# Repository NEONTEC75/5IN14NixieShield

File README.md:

# 5IN14NixieShield
This shield is just a minimal Nixie multiplexed circuit and contains the following components:
- 74141 nixie cathode driver IC (pins 4, 6, 7, 5);
- TLP627 opto-couplers for anodes (pins 12, 11, 9, 8, 10);
- 3-button resistive keyboard (A3);
- simple boost converter driven by Arduino's PWM (pin 3, and pin A0 for output voltage feedback);
- DS3231 module connector.

The library with some examples:
https://github.com/NEONTEC75/Nixie

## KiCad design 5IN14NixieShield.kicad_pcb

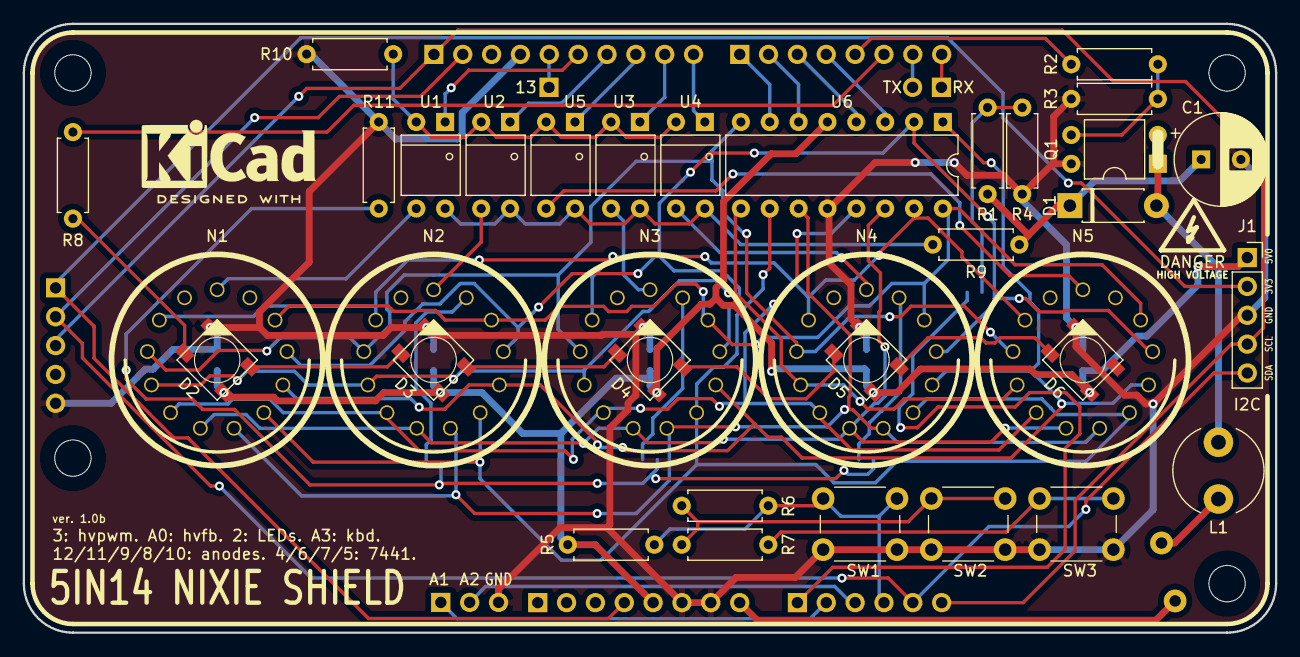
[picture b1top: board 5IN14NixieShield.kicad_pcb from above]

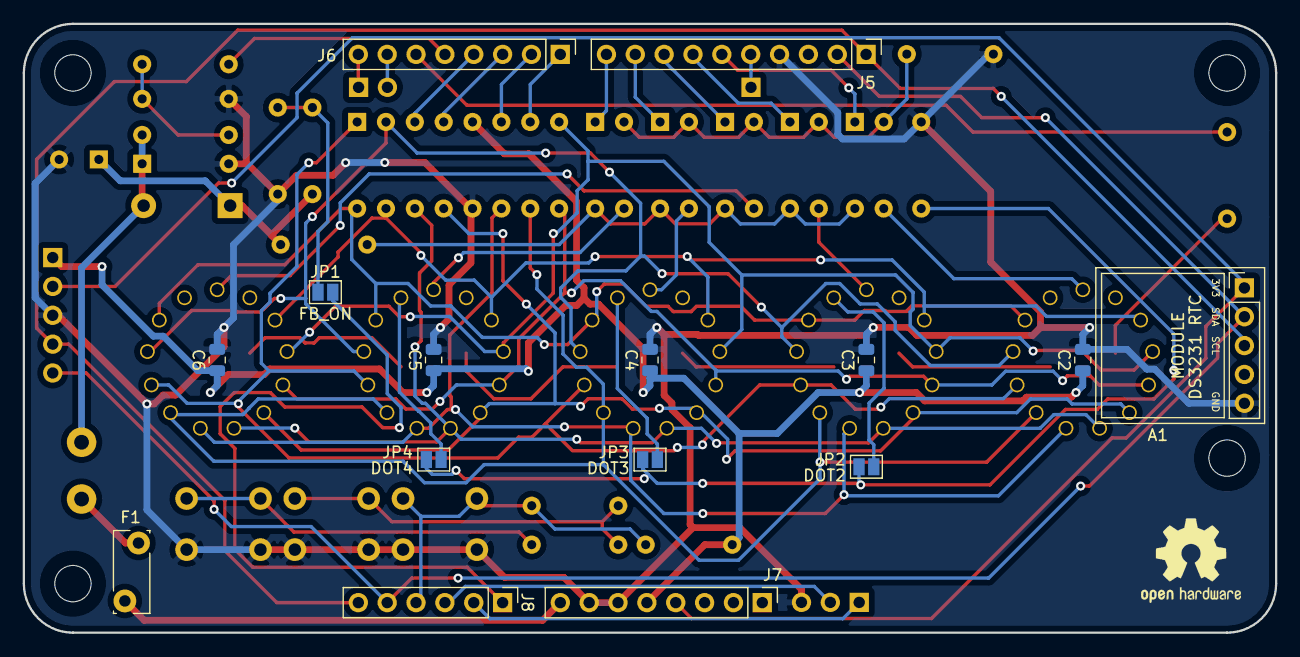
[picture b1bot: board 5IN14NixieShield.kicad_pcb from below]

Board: 2 copper layers, 110.2 x 53.6 mm, 59 parts (16 on the bottom side), 57 nets.

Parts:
A1: DS3231
C1: 4.7uF*350V; CP_Radial_D8.0mm_P3.50mm
C2, C3, C4, C5, C6: 100n; C_0805_2012Metric
D1: HER106; D_DO-41_SOD81_P7.62mm_Horizontal
D2, D3, D4, D5, D6: WS2812B
F1: 1A; Fuse_Bourns_MF-RG300
H1, H2, H3, H4: MountingHole; MountingHole_3.2mm_M3_DIN965
J1: I2C; PinSocket_1x05_P2.54mm_Vertical
J3: 13; PinHeader_1x01_P2.54mm_Vertical
J4: EXT2; PinHeader_1x02_P2.54mm_Vertical
J5: UNO3; PinHeader_1x10_P2.54mm_Vertical
J6: UNO4; PinHeader_1x08_P2.54mm_Vertical
J7: UNO1; PinHeader_1x08_P2.54mm_Vertical
J8: UNO2; PinHeader_1x06_P2.54mm_Vertical
J9: EXT1; PinHeader_1x03_P2.54mm_Vertical
JP1: FB_ON; SolderJumper-2_P1.3mm_Open_Pad1.0x1.5mm
JP2: DOT2; SolderJumper-2_P1.3mm_Open_Pad1.0x1.5mm
JP3: DOT3; SolderJumper-2_P1.3mm_Open_Pad1.0x1.5mm
JP4: DOT4; SolderJumper-2_P1.3mm_Open_Pad1.0x1.5mm
KICADLOGO: KiCad-Logo2_6mm_SilkScreen
L1: 470uH; L_Radial_D7.8mm_P5.00mm_Fastron_07HCP
N1, N2, N3, N4, N5: IN-14; IN-14new
OSHW1: OSHW-Logo2_9.8x8mm_SilkScreen
Q1: IRFD220; DIP-4_FET
R1: 300k; R_Axial_DIN0207_L6.3mm_D2.5mm_P7.62mm_Horizontal
R2: 22; R_Axial_DIN0207_L6.3mm_D2.5mm_P7.62mm_Horizontal
R3: 100k; R_Axial_DIN0207_L6.3mm_D2.5mm_P7.62mm_Horizontal
R4: 4k7; R_Axial_DIN0207_L6.3mm_D2.5mm_P7.62mm_Horizontal
R5, R6, R7: 10k; R_Axial_DIN0207_L6.3mm_D2.5mm_P7.62mm_Horizontal
R8: 100; R_Axial_DIN0207_L6.3mm_D2.5mm_P7.62mm_Horizontal
R9: 2k2; R_Axial_DIN0207_L6.3mm_D2.5mm_P7.62mm_Horizontal
R10: 470; R_Axial_DIN0207_L6.3mm_D2.5mm_P7.62mm_Horizontal
R11: 10k*; R_Axial_DIN0207_L6.3mm_D2.5mm_P7.62mm_Horizontal
SW1, SW2, SW3: SW_Push; SW_PUSH_6mm_H4.3mm
U1, U2, U3, U4, U5: TLP627
U6: K155ID1; DIP-16_W7.62mm

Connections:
+3V3: A1.1, J1.2, J7.4
+5V: C2.1, C3.1, C4.1, C5.1, C6.1, D2.1, D3.1, D4.1, D5.1, D6.1, J1.1, J7.5, R5.1, U6.5
/+HV: C1.1, D1.1, R1.2, R9.1
/A0: J8.1, JP1.2
/A1: J8.2, J9.1
/A2: J8.3, J9.2
/A3: J8.4, R5.2, R6.1, SW1.1
/A4: A1.2, J1.5, J5.2, J8.5
/A5: A1.3, J1.4, J5.1, J8.6
/ACTL_1: J5.6, U1.1
/ACTL_2: J5.7, U2.1
/ACTL_3: J5.9, U3.1
/ACTL_4: J5.10, U4.1
/ACTL_DOT: J5.8, U5.1
/BOOST_PWM: J6.5, R2.2
/D0: J4.1, J6.8
/D1: J4.2, J6.7
/D2: J6.6, R8.1
/D4: J6.4, U6.3
/D5: J6.3, U6.4
/D6: J6.2, U6.6
/D7: J6.1, U6.7
/D13: J3.1, J5.5
/NixieCtl/ANODE_1: N1.A, U1.3
/NixieCtl/ANODE_2: N2.A, U2.3
/NixieCtl/ANODE_3: N3.A, U3.3
/NixieCtl/ANODE_4: N4.A, U4.3
/NixieCtl/ANODE_5: N5.A, U5.3
/NixieCtl/CATHODE_0: N1.0, N2.0, N3.0, N4.0, N5.0, U6.16
/NixieCtl/CATHODE_1: N1.1, N2.1, N3.1, N4.1, N5.1, U6.15
/NixieCtl/CATHODE_2: N1.2, N2.2, N3.2, N4.2, N5.2, U6.8
/NixieCtl/CATHODE_3: N1.3, N2.3, N3.3, N4.3, N5.3, U6.9
/NixieCtl/CATHODE_4: N1.4, N2.4, N3.4, N4.4, N5.4, U6.13
/NixieCtl/CATHODE_5: N1.5, N2.5, N3.5, N4.5, N5.5, U6.14
/NixieCtl/CATHODE_6: N1.6, N2.6, N3.6, N4.6, N5.6, U6.11
/NixieCtl/CATHODE_7: N1.7, N2.7, N3.7, N4.7, N5.7, U6.10
/NixieCtl/CATHODE_8: N1.8, N2.8, N3.8, N4.8, N5.8, U6.1
/NixieCtl/CATHODE_9: N1.9, N2.9, N3.9, N4.9, N5.9, U6.2
/VIN: F1.1, J7.8
GND: A1.5, C1.2, C2.2, C3.2, C4.2, C5.2, C6.2, D2.3, D3.3, D4.3, D5.3, D6.3, J1.3, J5.4, J7.6, J7.7, J9.3, Q1.3, R3.2, R4.1, R10.2, R11.1, SW1.2, SW2.2, SW3.2, U6.12
unnamed: D1.2, L1.1, Q1.2
unnamed: D2.2, D3.4
unnamed: D2.4, R8.2
unnamed: D3.2, D4.4
unnamed: D4.2, D5.4
unnamed: D5.2, D6.4
unnamed: F1.2, L1.2
unnamed: JP1.1, R1.1, R4.2
unnamed: JP2.1, N2.RHDP
unnamed: JP2.2, JP3.2, JP4.2, R11.2
unnamed: JP3.1, N3.RHDP
unnamed: JP4.1, N4.RHDP
unnamed: Q1.1, R2.1, R3.1
unnamed: R6.2, R7.1, SW2.1
unnamed: R7.2, SW3.1
unnamed: R9.2, U1.4, U2.4, U3.4, U4.4, U5.4
unnamed: R10.1, U1.2, U2.2, U3.2, U4.2, U5.2

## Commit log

2020-08-10 Slightly optimized components placement. Added jumpers to enable decimal points (for thermometers). Updated some footprints.
